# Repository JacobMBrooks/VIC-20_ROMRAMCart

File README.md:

# VIC-20_ROMRAMCart
**Universal ROM/RAM Cartridge for the Commodore VIC-20**

Though there are many existing open-source board designs for Commodore VIC-20 ROM or RAM expansion cartridges, I wanted one that could function either as a ROM program cartridge, a customizable RAM expansion cartridge, or as any combination of those things. Many on-demand PCB manufacturers require you to order 5 or more boards at a time; this design allows me to order the same PCB for all of the cartridge types I want to make. I am aware that this is not the simplest or cheapest way to do this, it just happens to be the solution that fulfilled my requirements. 

STL files for a 3D-printable cartridge enclosure are included here, curteousy of my amazing partner.

Of course, this design comes with no guarantees of any sort. I can confirm that the PCBs have been tested and work in my 1983 NTSC VIC-20 and expect that there would be no issues in a PAL system. If anyone finds problems with this design, please let me know or open an issue.

Overview
--

This board can fill BLK1, BLK2, BLK3, and BLK5 with either a 2764 8k EPROM or a 6264 8k SRAM chip. This way, ROM and RAM can be mixed/matched/inserted wherever is necessary for the cartridge. A 6264 SRAM chip can be used along with a 74LS08 IC to fill RAM1, RAM2, and RAM3 blocks to form a 3k expansion. In this configuration, the remaining 5k of the SRAM chip is left unused. This board, therefore, can be populated to be:

- A 3k, 8k, 16k, 24k, 32k, or 35k RAM expansion cartridge
- An 8k, 16k, 24k, or 32k ROM cartridge
- A cartridge containing some combination of ROM/RAM

Details in the section below.

Configurations
--
In the VIC-20, the BLK1, BLK2, BLK3, BLK5, and 3k ram area can be thought of as operating independently of one another. This means that, with the exception of the 3k RAM area, either RAM or ROM can be placed in any of these positions. As far as I am aware, the 3k RAM area (RAM1, RAM2, RAM3) is designed to only contain RAM. It is possible, therefore, to set a cartridge up in a variety of different configurations. This PCB is designed to support them all. 

For those who want to be able to re-configure the board with ease, pads are provided for typical 0.1-inch-pitch pin headers to be used with removable jumpers. The ICs can be socketed for easy swapping. If the board is to be set in a permanent configuration, solder bridge pads are also provided. 

- **35k RAM expansion configuration**: 
  - To populate all available addresses with RAM, install 6264 SRAM ICs in all 32-pin IC positions
  - The 3k RAM area also requires the 74LS08 IC to be populated
  - All solder bridges/jumpers need to be set to the SRAM position
- **8k/16k/32k ROM cartridge configuration** 
  - ROM images are usually designed to be available at a particular address. It is therefore important that you install the EPROMs in the position required. 
  - The 3k RAM area is unused in this configuration. The 74LS08 IC can be omitted. 
  - Solder bridges/jumpers must be set to the EPROM position
- **Some other combination of ROM/RAM**
  - Some cartridges are designed to contain both ROM and RAM. For example, the VIC-1211A Super Expander cartridge contained BASIC extensions as well as 3k of RAM expansion. I believe that some assembler cartridges worked in the same way.
  - If you need the 3k RAM expansion, install the 6264 SRAM chip and the 74LS08. If you don't need it then don't install it.
  - Install 2764 EPROM or 6264 SRAM ICs in whatever positions are required and be sure to set the solder bridges/jumpers to the appropriate position.
 
**NOTE**: The VIC-20 won't report all of a 35k RAM cartridge in "BYTES FREE" at the top of the screen. When the system sees RAM in BLK1/2/3/5, BASIC seems to assume that there is none in the 3k area. 

PCB Manufacturing
--
Gerber files are included in the Kicad directory. For best long-term performance, I recommend ENIG coating for the edge connector fingers; solder alone will oxidize over time and will likely need cleaning eventually. I also recommend that the PCBs are 1.6mm thick, though there is likely some wiggle room here.

It is important that the PCB edge connector is beveled. I ordered the boards with a 45-degree bevels, though you could do this with a file if you want to save a tiny bit of money. Boards without bevels could damage the fingers in the motherboard edge connector, so please don't skip this step.

3D-printed case
--

As mentioned before, my amazing partner designed a 3D-printable case suitable for protecting the boards in this repo. It is important to note that this enclosure will ***not*** fit normal VIC-20 cartridge PCBs without modification.

Each case will require:
- 1x print of the top cover
- 1x print of the bottom cover
- 3x M3 heat set inserts
- 3x M3x8mm countersink machine screws

Depending on your printer tolerances, you may need to pad the top PCB edge with a bit of tape to prevent the board from rotating about the center screw. I have printed this case on two printers, one needed no padding and the other needed ~1mm of tape thickness. The case top has a deep cutout to accommodate tall EPROMs in sockets. You should be able to use any standard size IC.

I use a soldering iron to install the heat set inserts. Be gentile and wait until the inserts fully cool before trying to assemble the cartridge. Though I know that we are all super excited to play our games, we must exercise a little patience here.

License
--
This work is licensed under a [Creative Commons Attribution-ShareAlike 4.0 International License](https://creativecommons.org/licenses/by-sa/4.0/). 

This design utilizes the VIC-20 expansion port edge connector footprint from [https://github.com/hackup/HackupNet-KiCad-Libraries](https://github.com/hackup/HackupNet-KiCad-Libraries), also distributed under the same license.

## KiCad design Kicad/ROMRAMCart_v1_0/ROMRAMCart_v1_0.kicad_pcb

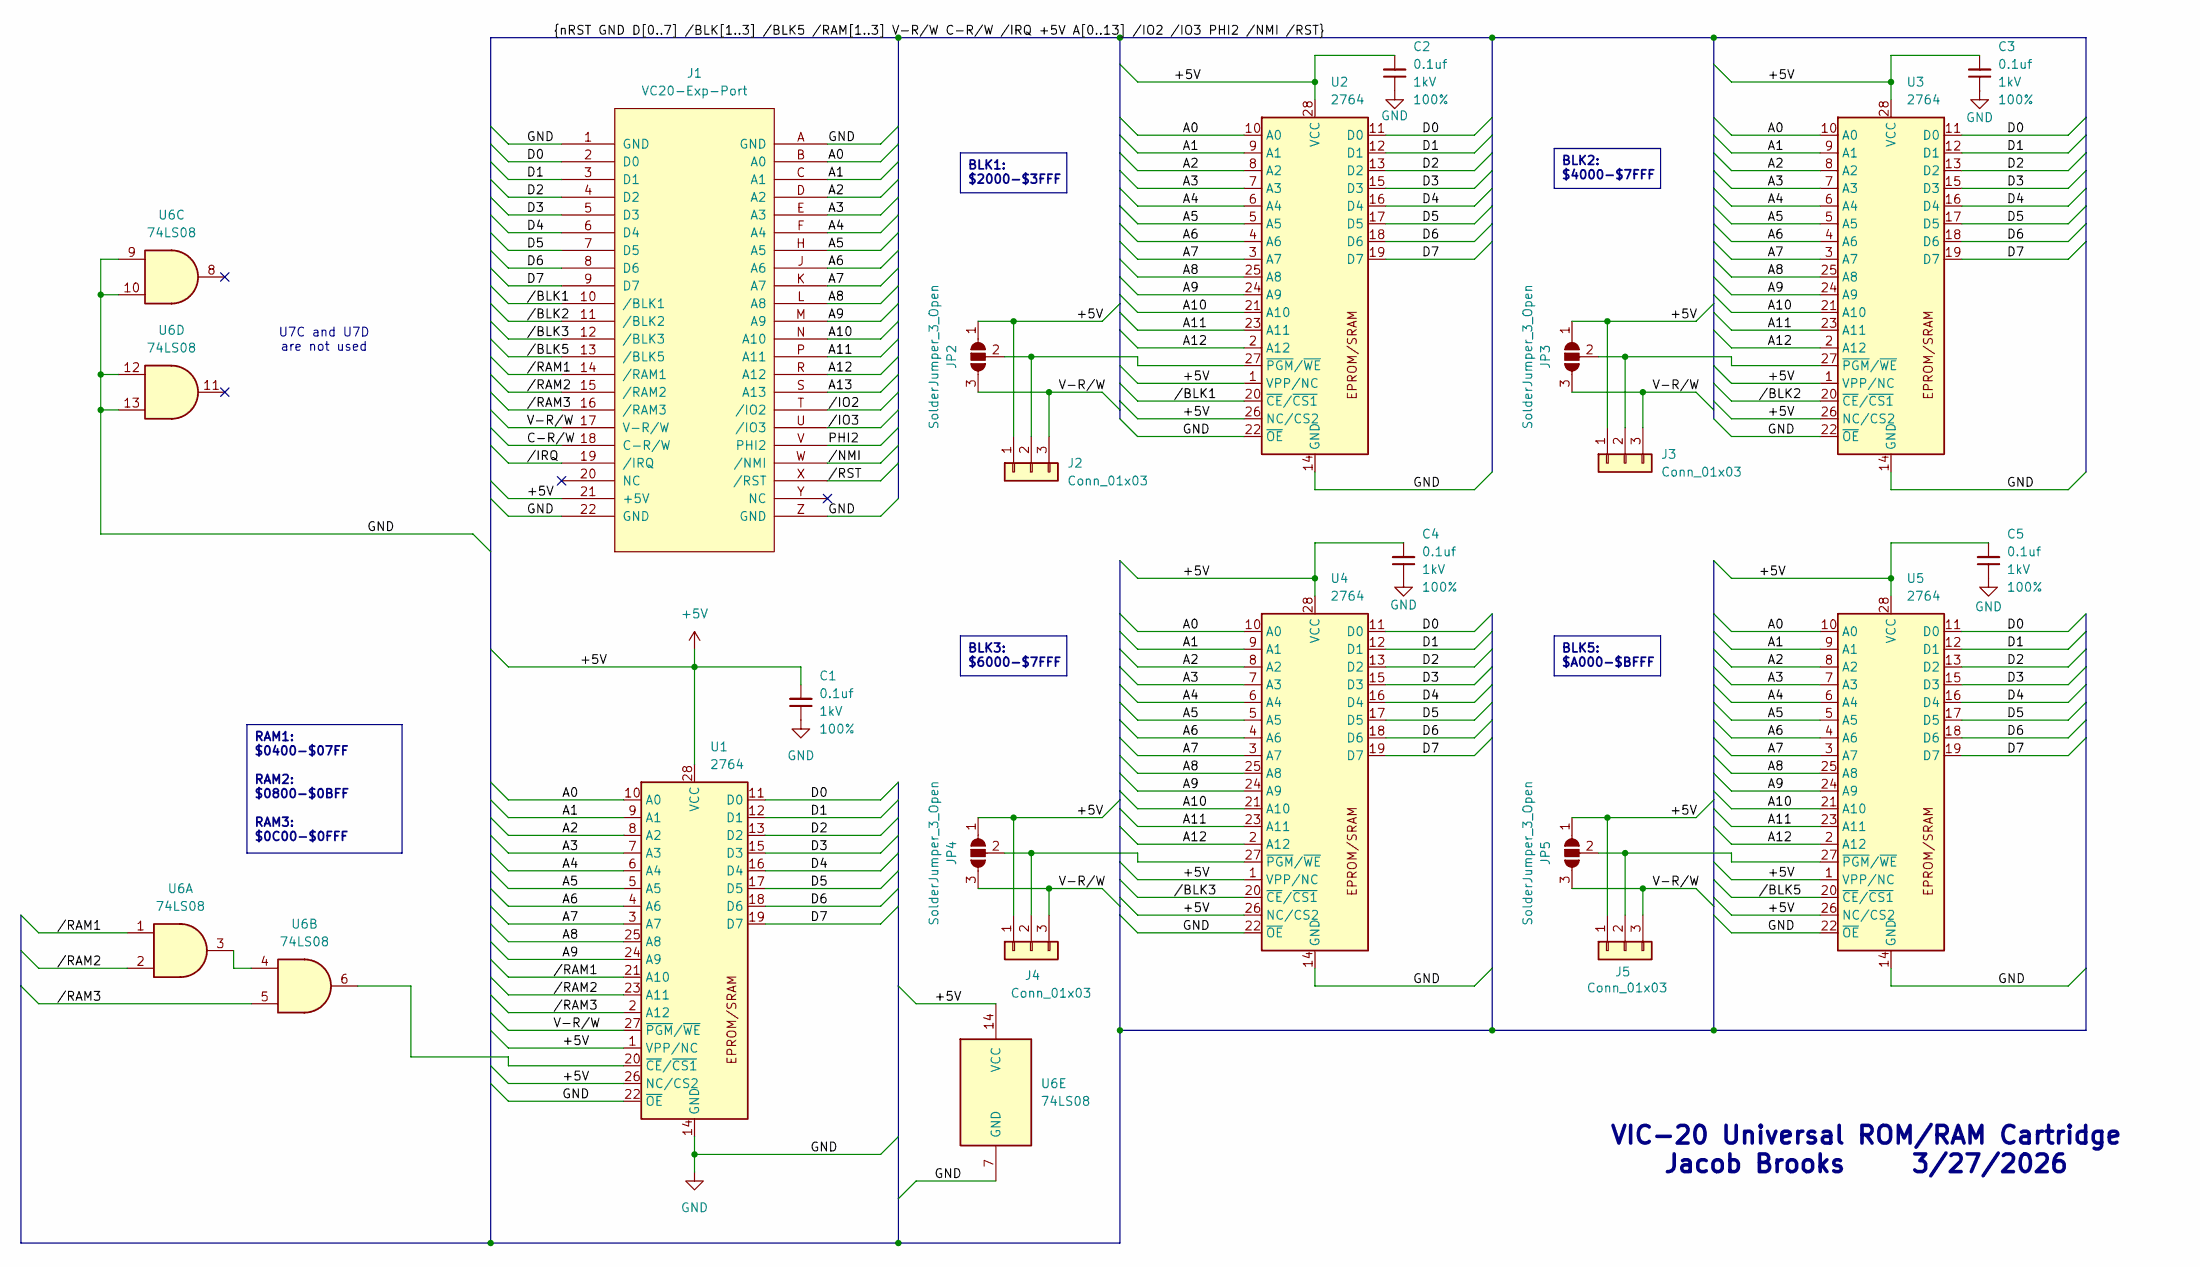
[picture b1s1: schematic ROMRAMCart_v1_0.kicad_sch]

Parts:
C1, C2, C3, C4, C5: 0.1uf; C_Disc_D5.0mm_W2.5mm_P5.00mm; Voltage 1kV; Tolerance 100%
J1: VC20-Exp-Port; VC20-Cart
J2, J3, J4, J5: Conn_01x03; PinHeader_1x03_P2.54mm_Vertical
JP2, JP3, JP4, JP5: SolderJumper_3_Open; SolderJumper-3_P1.3mm_Open_Pad1.0x1.5mm
U1, U2, U3, U4, U5: 2764; DIP-28_W15.24mm
U6: 74LS08; DIP-14_W7.62mm

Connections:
+5V: C1.2, C2.2, C3.2, C4.2, C5.2, J1.21 (+5V), J2.1, J3.1, J4.1, J5.1, JP2.1 (A), JP3.1 (A), JP4.1 (A), JP5.1 (A), U1.1 (VPP/NC), U1.26 (NC/CS2), U1.28 (VCC), U2.1 (VPP/NC), U2.26 (NC/CS2), U2.28 (VCC), U3.1 (VPP/NC), U3.26 (NC/CS2), U3.28 (VCC), U4.1 (VPP/NC), U4.26 (NC/CS2), U4.28 (VCC), U5.1 (VPP/NC), U5.26 (NC/CS2), U5.28 (VCC), U6.14 (VCC)
/A0: J1.B (A0), U1.10 (A0), U2.10 (A0), U3.10 (A0), U4.10 (A0), U5.10 (A0)
/A1: J1.C (A1), U1.9 (A1), U2.9 (A1), U3.9 (A1), U4.9 (A1), U5.9 (A1)
/A2: J1.D (A2), U1.8 (A2), U2.8 (A2), U3.8 (A2), U4.8 (A2), U5.8 (A2)
/A3: J1.E (A3), U1.7 (A3), U2.7 (A3), U3.7 (A3), U4.7 (A3), U5.7 (A3)
/A4: J1.F (A4), U1.6 (A4), U2.6 (A4), U3.6 (A4), U4.6 (A4), U5.6 (A4)
/A5: J1.H (A5), U1.5 (A5), U2.5 (A5), U3.5 (A5), U4.5 (A5), U5.5 (A5)
/A6: J1.J (A6), U1.4 (A6), U2.4 (A6), U3.4 (A6), U4.4 (A6), U5.4 (A6)
/A7: J1.K (A7), U1.3 (A7), U2.3 (A7), U3.3 (A7), U4.3 (A7), U5.3 (A7)
/A8: J1.L (A8), U1.25 (A8), U2.25 (A8), U3.25 (A8), U4.25 (A8), U5.25 (A8)
/A9: J1.M (A9), U1.24 (A9), U2.24 (A9), U3.24 (A9), U4.24 (A9), U5.24 (A9)
/A10: J1.N (A10), U2.21 (A10), U3.21 (A10), U4.21 (A10), U5.21 (A10)
/A11: J1.P (A11), U2.23 (A11), U3.23 (A11), U4.23 (A11), U5.23 (A11)
/A12: J1.R (A12), U2.2 (A12), U3.2 (A12), U4.2 (A12), U5.2 (A12)
/A13: J1.S (A13)
/C-R/W: J1.18 (C-R/W)
/D0: J1.2 (D0), U1.11 (D0), U2.11 (D0), U3.11 (D0), U4.11 (D0), U5.11 (D0)
/D1: J1.3 (D1), U1.12 (D1), U2.12 (D1), U3.12 (D1), U4.12 (D1), U5.12 (D1)
/D2: J1.4 (D2), U1.13 (D2), U2.13 (D2), U3.13 (D2), U4.13 (D2), U5.13 (D2)
/D3: J1.5 (D3), U1.15 (D3), U2.15 (D3), U3.15 (D3), U4.15 (D3), U5.15 (D3)
/D4: J1.6 (D4), U1.16 (D4), U2.16 (D4), U3.16 (D4), U4.16 (D4), U5.16 (D4)
/D5: J1.7 (D5), U1.17 (D5), U2.17 (D5), U3.17 (D5), U4.17 (D5), U5.17 (D5)
/D6: J1.8 (D6), U1.18 (D6), U2.18 (D6), U3.18 (D6), U4.18 (D6), U5.18 (D6)
/D7: J1.9 (D7), U1.19 (D7), U2.19 (D7), U3.19 (D7), U4.19 (D7), U5.19 (D7)
/PHI2: J1.V (PHI2)
/V-R/W: J1.17 (V-R/W), J2.3, J3.3, J4.3, J5.3, JP2.3 (B), JP3.3 (B), JP4.3 (B), JP5.3 (B), U1.27 (~PGM/~WE)
//BLK1: J1.10 (/BLK1), U2.20 (~CE/~CS1)
//BLK2: J1.11 (/BLK2), U3.20 (~CE/~CS1)
//BLK3: J1.12 (/BLK3), U4.20 (~CE/~CS1)
//BLK5: J1.13 (/BLK5), U5.20 (~CE/~CS1)
//IO2: J1.T (/IO2)
//IO3: J1.U (/IO3)
//IRQ: J1.19 (/IRQ)
//NMI: J1.W (/NMI)
//RAM1: J1.14 (/RAM1), U1.21 (A10), U6.1
//RAM2: J1.15 (/RAM2), U1.23 (A11), U6.2
//RAM3: J1.16 (/RAM3), U1.2 (A12), U6.5
//RST: J1.X (/RST)
GND: C1.1, C2.1, C3.1, C4.1, C5.1, J1.1 (GND), J1.22 (GND), J1.A (GND), J1.Z (GND), U1.14 (GND), U1.22 (~OE), U2.14 (GND), U2.22 (~OE), U3.14 (GND), U3.22 (~OE), U4.14 (GND), U4.22 (~OE), U5.14 (GND), U5.22 (~OE), U6.7 (GND), U6.9, U6.10, U6.12, U6.13
unnamed: J2.2, JP2.2 (C), U2.27 (~PGM/~WE)
unnamed: J3.2, JP3.2 (C), U3.27 (~PGM/~WE)
unnamed: J4.2, JP4.2 (C), U4.27 (~PGM/~WE)
unnamed: J5.2, JP5.2 (C), U5.27 (~PGM/~WE)
unnamed: U1.20 (~CE/~CS1), U6.6
unnamed: U6.3, U6.4

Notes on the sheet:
VIC-20 Universal ROM/RAM Cartridge Jacob Brooks 3/27/2026
U7C and U7D are not used
RAM1: $0400-$07FF RAM2: $0800-$0BFF RAM3: $0C00-$0FFF
BLK3: $6000-$7FFF
BLK2: $4000-$7FFF
BLK1: $2000-$3FFF
BLK5: $A000-$BFFF

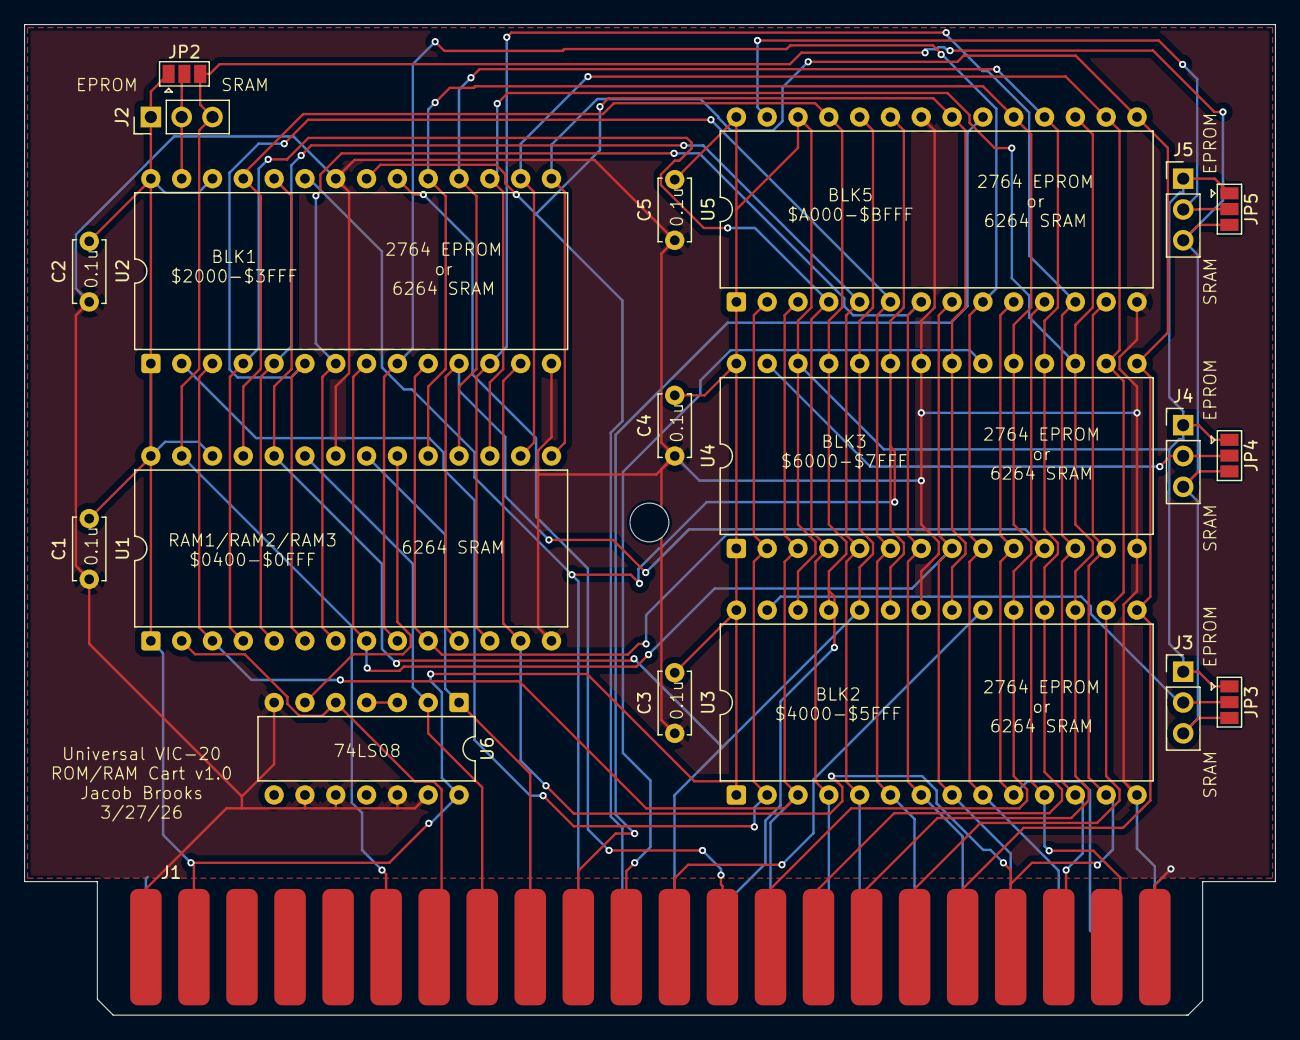
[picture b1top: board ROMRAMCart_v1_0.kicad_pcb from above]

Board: 2 copper layers, 103.1 x 81.6 mm, 21 parts (0 on the bottom side), 37 nets.

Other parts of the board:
REF0: MountingHole_3.2mm_M3_DIN965

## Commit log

2026-04-10 Add files via upload
    Initial commit, added main files
